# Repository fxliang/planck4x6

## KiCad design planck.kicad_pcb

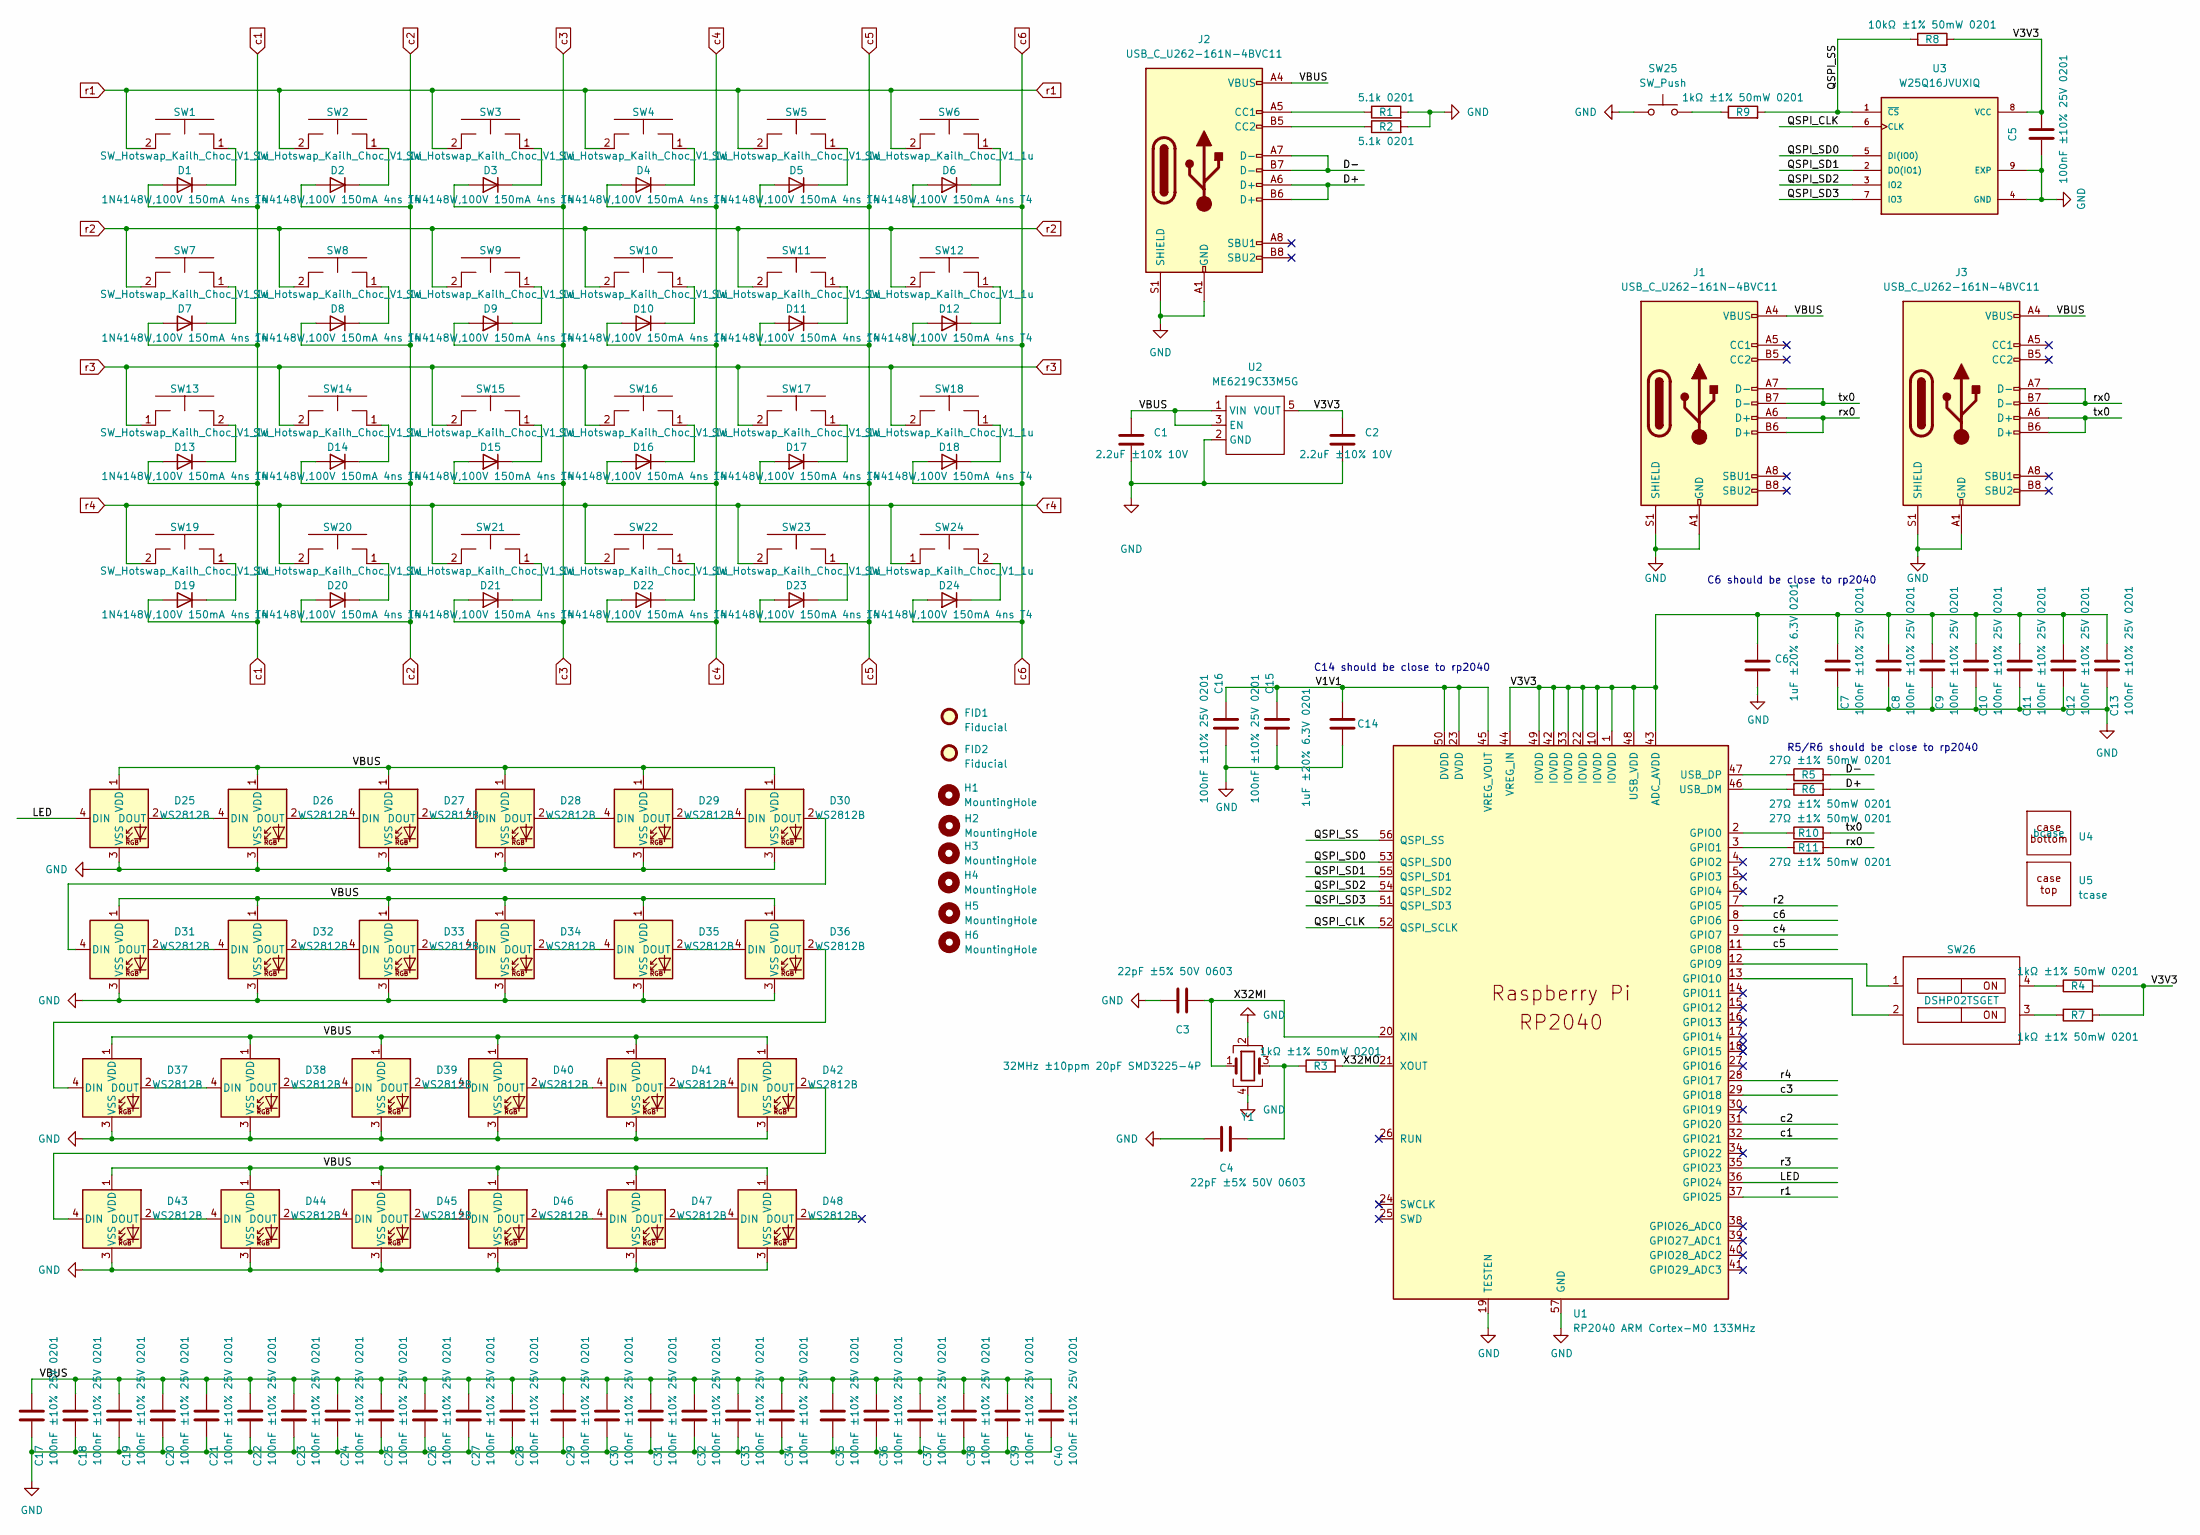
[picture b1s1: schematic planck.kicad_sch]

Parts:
C1, C2: 2.2uF ±10% 10V; R_0201_0603Metric; JLC C335106
C3, C4: 22pF ±5% 50V 0603; R_0201_0603Metric; JLC C76960
C5, C7, C8, C9, C10, C11, C12, C13, C15, C16, C17, C18, C19, C20, C21, C22, C23, C24, C25, C26, C27, C28, C29, C30, C31, C32, C33, C34, C35, C36, C37, C38, C39, C40: 100nF ±10% 25V 0201; R_0201_0603Metric; JLC C76939
C6, C14: 1uF ±20% 6.3V 0201; C_0201_0603Metric; JLC C87143
D1, D2, D3, D4, D5, D6, D7, D8, D9, D10, D11, D12, D13, D14, D15, D16, D17, D18, D19, D20, D21, D22, D23, D24: 1N4148W,100V 150mA 4ns T4; D_SOD-123; JLC C2099
D25, D26, D27, D28, D29, D30, D31, D32, D33, D34, D35, D36, D37, D38, D39, D40, D41, D42, D43, D44, D45, D46, D47, D48: WS2812B; WS2812_6028_REV_S
FID1, FID2: Fiducial; Fiducial_0.5mm_Mask1.5mm
H1, H2, H3, H4, H5, H6: MountingHole; MountingHole_2.2mm_M2
J1, J2, J3: USB_C_U262-161N-4BVC11; USB_C_TYPE-C-31-M-14; MPN U262-161N-4BVC11; JLC C223907
R1, R2: 5.1k 0201; R_0201_0603Metric; JLC C473460
R3, R4, R7, R9: 1kΩ ±1% 50mW 0201; R_0201_0603Metric; JLC C138165
R5, R6, R10, R11: 27Ω ±1% 50mW 0201; R_0201_0603Metric; JLC C273268
R8: 10kΩ ±1% 50mW 0201; R_0201_0603Metric; JLC C106225
SW1, SW2, SW3, SW4, SW5, SW6, SW7, SW8, SW9, SW10, SW11, SW12, SW13, SW14, SW15, SW16, SW17, SW18, SW19, SW20, SW21, SW22, SW23, SW24: SW_Hotswap_Kailh_Choc_V1_1u; SW_Hotswap_Kailh_Choc_V1
SW25: SW_Push; B3U-1000P; JLC C231329
SW26: DSHP02TSGET; JLC C40735
U1: RP2040 ARM Cortex-M0 133MHz; RP2040-QFN-56; JLC C2040
U2: ME6219C33M5G; SOT-23-5; JLC C47382
U3: W25Q16JVUXIQ; SON-8-1EP_3x2mm_P0.5mm_EP1.4x1.6mm; JLC C2843335
U4: bcase
U5: tcase
Y1: 32MHz ±10ppm 20pF SMD3225-4P; Crystal_SMD_3225-4Pin_3.2x2.5mm; JLC C164054

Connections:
/D+: J2.A6 (D+), J2.B6 (D+), R6.2
/D-: J2.A7 (D-), J2.B7 (D-), R5.2
/LED: D25.4 (DIN), U1.36 (GPIO24)
/QSPI_CLK: U1.52 (QSPI_SCLK), U3.6 (CLK)
/QSPI_SD0: U1.53 (QSPI_SD0), U3.5 (DI(IO0))
/QSPI_SD1: U1.55 (QSPI_SD1), U3.2 (DO(IO1))
/QSPI_SD2: U1.54 (QSPI_SD2), U3.3 (IO2)
/QSPI_SD3: U1.51 (QSPI_SD3), U3.7 (IO3)
/QSPI_SS: R8.1, R9.2, U1.56 (QSPI_SS), U3.1 (~CS)
/V1V1: C14.2, C15.1, C16.1, U1.23 (DVDD), U1.45 (VREG_VOUT), U1.50 (DVDD)
/V3V3: C2.1, C5.2, C6.1, C7.2, C8.2, C9.2, C10.2, C11.2, C12.2, C13.2, R4.2, R7.2, R8.2, U1.1 (IOVDD), U1.10 (IOVDD), U1.22 (IOVDD), U1.33 (IOVDD), U1.42 (IOVDD), U1.43 (ADC_AVDD), U1.44 (VREG_IN), U1.48 (USB_VDD), U1.49 (IOVDD), U2.5 (VOUT), U3.8 (VCC)
/VBUS: C1.1, C17.2, C18.2, C19.2, C20.2, C21.2, C22.2, C23.2, C24.2, C25.2, C26.2, C27.2, C28.2, C29.2, C30.2, C31.2, C32.2, C33.2, C34.2, C35.2, C36.2, C37.2, C38.2, C39.2, C40.2, D25.1 (VDD), D26.1 (VDD), D27.1 (VDD), D28.1 (VDD), D29.1 (VDD), D30.1 (VDD), D31.1 (VDD), D32.1 (VDD), D33.1 (VDD), D34.1 (VDD), D35.1 (VDD), D36.1 (VDD), D37.1 (VDD), D38.1 (VDD), D39.1 (VDD), D40.1 (VDD), D41.1 (VDD), D42.1 (VDD), D43.1 (VDD), D44.1 (VDD), D45.1 (VDD), D46.1 (VDD), D47.1 (VDD), D48.1 (VDD), J1.A4 (VBUS), J1.A9 (VBUS), J1.B4 (VBUS), J1.B9 (VBUS), J2.A4 (VBUS), J2.A9 (VBUS), J2.B4 (VBUS), J2.B9 (VBUS), J3.A4 (VBUS), J3.A9 (VBUS), J3.B4 (VBUS), J3.B9 (VBUS), U2.1 (VIN), U2.3 (EN)
/X32MI: C3.1, U1.20 (XIN), Y1.1
/X32MO: R3.2, U1.21 (XOUT)
/rx0: J1.A6 (D+), J1.B6 (D+), J3.A7 (D-), J3.B7 (D-), R11.2
/tx0: J1.A7 (D-), J1.B7 (D-), J3.A6 (D+), J3.B6 (D+), R10.2
GND: C1.2, C2.2, C3.2, C4.2, C5.1, C6.2, C7.1, C8.1, C9.1, C10.1, C11.1, C12.1, C13.1, C14.1, C15.2, C16.2, C17.1, C18.1, C19.1, C20.1, C21.1, C22.1, C23.1, C24.1, C25.1, C26.1, C27.1, C28.1, C29.1, C30.1, C31.1, C32.1, C33.1, C34.1, C35.1, C36.1, C37.1, C38.1, C39.1, C40.1, D25.3 (VSS), D26.3 (VSS), D27.3 (VSS), D28.3 (VSS), D29.3 (VSS), D30.3 (VSS), D31.3 (VSS), D32.3 (VSS), D33.3 (VSS), D34.3 (VSS), D35.3 (VSS), D36.3 (VSS), D37.3 (VSS), D38.3 (VSS), D39.3 (VSS), D40.3 (VSS), D41.3 (VSS), D42.3 (VSS), D43.3 (VSS), D44.3 (VSS), D45.3 (VSS), D46.3 (VSS), D47.3 (VSS), D48.3 (VSS), J1.A1 (GND), J1.A12 (GND), J1.B1 (GND), J1.B12 (GND), J1.S1 (SHIELD), J2.A1 (GND), J2.A12 (GND), J2.B1 (GND), J2.B12 (GND), J2.S1 (SHIELD), J3.A1 (GND), J3.A12 (GND), J3.B1 (GND), J3.B12 (GND), J3.S1 (SHIELD), R1.2, R2.2, SW25.1, U1.19 (TESTEN), U1.57 (GND), U2.2 (GND), U3.4 (GND), U3.9 (EXP), Y1.2, Y1.4
unnamed: C4.1, R3.1, Y1.3
unnamed: D1.1 (K), SW1.1
unnamed: D2.1 (K), SW2.1
unnamed: D3.1 (K), SW3.1
unnamed: D4.1 (K), SW4.1
unnamed: D5.1 (K), SW5.1
unnamed: D6.1 (K), SW6.1
unnamed: D7.1 (K), SW7.1
unnamed: D8.1 (K), SW8.1
unnamed: D9.1 (K), SW9.1
unnamed: D10.1 (K), SW10.1
unnamed: D11.1 (K), SW11.1
unnamed: D12.1 (K), SW12.1
unnamed: D13.1 (K), SW13.2
unnamed: D14.1 (K), SW14.1
unnamed: D15.1 (K), SW15.1
unnamed: D16.1 (K), SW16.1
unnamed: D17.1 (K), SW17.1
unnamed: D18.1 (K), SW18.1
unnamed: D19.1 (K), SW19.1
unnamed: D20.1 (K), SW20.1
unnamed: D21.1 (K), SW21.1
unnamed: D22.1 (K), SW22.1
unnamed: D23.1 (K), SW23.1
unnamed: D24.1 (K), SW24.2
unnamed: D25.2 (DOUT), D26.4 (DIN)
unnamed: D26.2 (DOUT), D27.4 (DIN)
unnamed: D27.2 (DOUT), D28.4 (DIN)
unnamed: D28.2 (DOUT), D29.4 (DIN)
unnamed: D29.2 (DOUT), D30.4 (DIN)
unnamed: D30.2 (DOUT), D31.4 (DIN)
unnamed: D31.2 (DOUT), D32.4 (DIN)
unnamed: D32.2 (DOUT), D33.4 (DIN)
unnamed: D33.2 (DOUT), D34.4 (DIN)
unnamed: D34.2 (DOUT), D35.4 (DIN)
unnamed: D35.2 (DOUT), D36.4 (DIN)
unnamed: D36.2 (DOUT), D37.4 (DIN)
unnamed: D37.2 (DOUT), D38.4 (DIN)
unnamed: D38.2 (DOUT), D39.4 (DIN)
unnamed: D39.2 (DOUT), D40.4 (DIN)
unnamed: D40.2 (DOUT), D41.4 (DIN)
unnamed: D41.2 (DOUT), D42.4 (DIN)
unnamed: D42.2 (DOUT), D43.4 (DIN)
unnamed: D43.2 (DOUT), D44.4 (DIN)
unnamed: D44.2 (DOUT), D45.4 (DIN)
unnamed: D45.2 (DOUT), D46.4 (DIN)
unnamed: D46.2 (DOUT), D47.4 (DIN)
unnamed: D47.2 (DOUT), D48.4 (DIN)
unnamed: J2.A5 (CC1), R1.1
unnamed: J2.B5 (CC2), R2.1
unnamed: R4.1, SW26.4
unnamed: R7.1, SW26.3
unnamed: R9.1, SW25.2
unnamed: R10.1, U1.2 (GPIO0)
unnamed: R11.1, U1.3 (GPIO1)
unnamed: SW26.1, U1.12 (GPIO9)
unnamed: SW26.2, U1.13 (GPIO10)
unnamed: R6.1, U1.46 (USB_DM)
unnamed: R5.1, U1.47 (USB_DP)
c1: D1.2 (A), D7.2 (A), D13.2 (A), D19.2 (A), U1.32 (GPIO21)
c2: D2.2 (A), D8.2 (A), D14.2 (A), D20.2 (A), U1.31 (GPIO20)
c3: D3.2 (A), D9.2 (A), D15.2 (A), D21.2 (A), U1.29 (GPIO18)
c4: D4.2 (A), D10.2 (A), D16.2 (A), D22.2 (A), U1.9 (GPIO7)
c5: D5.2 (A), D11.2 (A), D17.2 (A), D23.2 (A), U1.11 (GPIO8)
c6: D6.2 (A), D12.2 (A), D18.2 (A), D24.2 (A), U1.8 (GPIO6)
r1: SW1.2, SW2.2, SW3.2, SW4.2, SW5.2, SW6.2, U1.37 (GPIO25)
r2: SW7.2, SW8.2, SW9.2, SW10.2, SW11.2, SW12.2, U1.7 (GPIO5)
r3: SW13.1, SW14.2, SW15.2, SW16.2, SW17.2, SW18.2, U1.35 (GPIO23)
r4: SW19.2, SW20.2, SW21.2, SW22.2, SW23.2, SW24.1, U1.28 (GPIO17)

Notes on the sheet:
R5/R6 should be close to rp2040
C6 should be close to rp2040
C14 should be close to rp2040

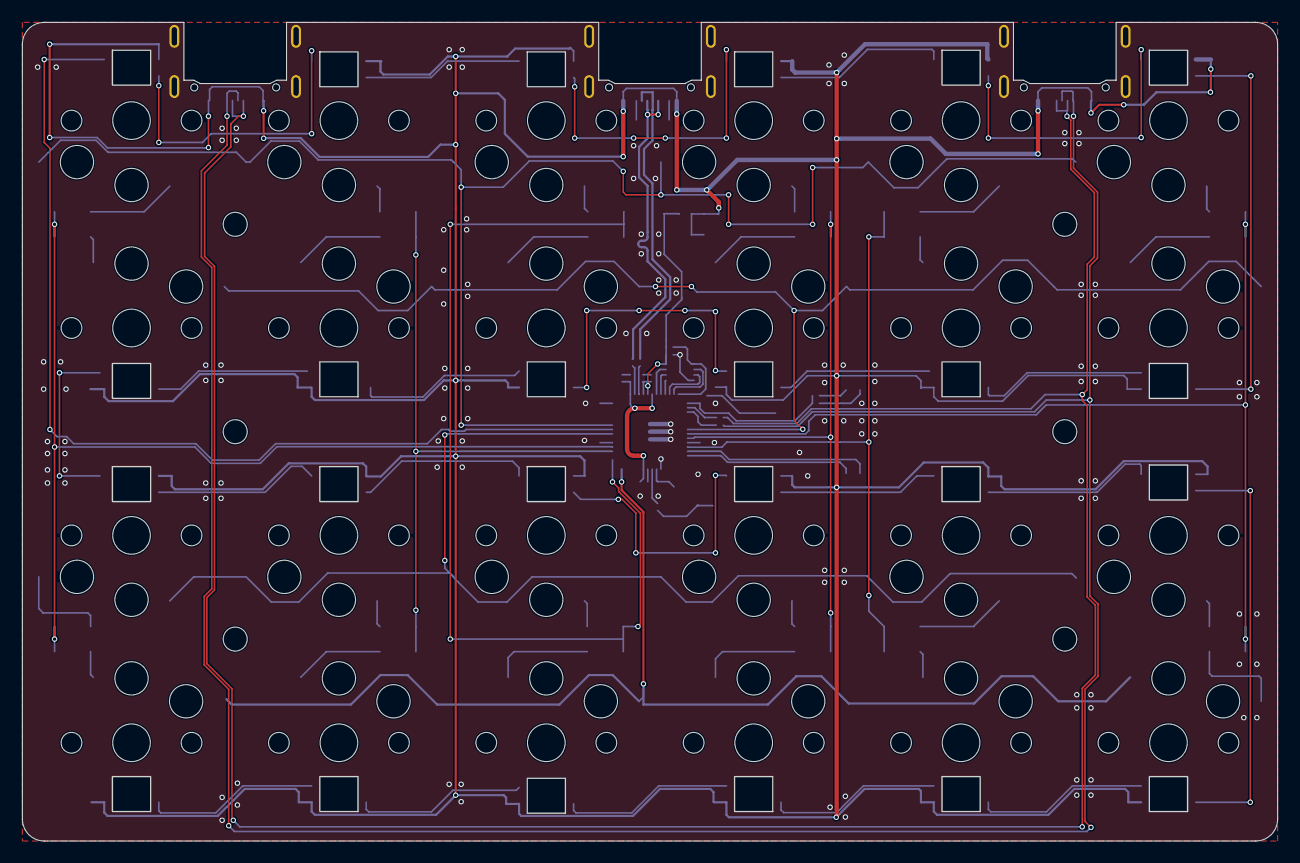
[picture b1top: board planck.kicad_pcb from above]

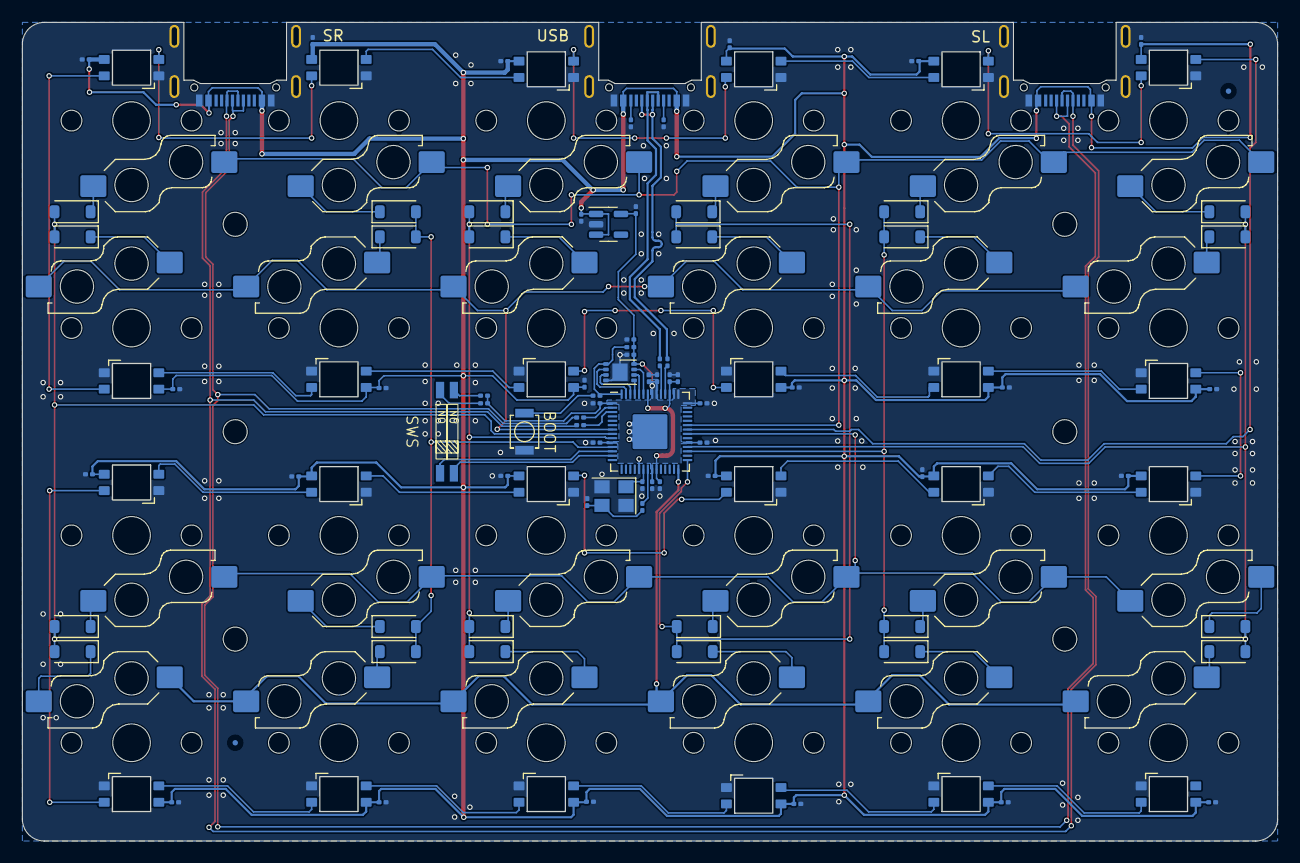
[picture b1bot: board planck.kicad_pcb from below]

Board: 2 copper layers, 115.0 x 75.0 mm, 142 parts (87 on the bottom side), 86 nets.

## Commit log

2023-02-07 first commit, key layout, usb/trrs layout.
2023-02-09 some modifications
2023-02-09 add ignore
2023-02-10 MX version complete
2023-02-10 add libraries
2023-02-10 add choc libraries
2023-02-13 main layouts
2023-02-14 pico with solder choc v1
2023-02-16 core board sketch
2023-02-17 layout
2023-02-17 almost done
2023-02-17 ADD SWITCH HANDSET
2023-02-17 hide switch print
2023-02-18 connect LED, add case
2023-02-18 filet top case
2023-02-21 distance check add serial resistor for protection
2023-02-23 little layout modification resistor over serial for protection 27R
